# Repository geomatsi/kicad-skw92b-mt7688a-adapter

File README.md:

# Breadboard adapter for SKW92B WiFi module

Kicad project for [SKW92B](http://www.skylab.com.cn/uploadfile/Download/SkyLab_SKW92B_V1.06_datasheet.pdf) MT7688a WiFi module breadboard adapter.
SKW92B module integrates a 1x1 802.11n Wi-Fi radio, 580MHz MIPS CPU, 1-port Ethernet PHY, USB2.0 host, I2C/PCM and multiple slow GPIOs. 

Adapter schematics:

Adapter 3D view:

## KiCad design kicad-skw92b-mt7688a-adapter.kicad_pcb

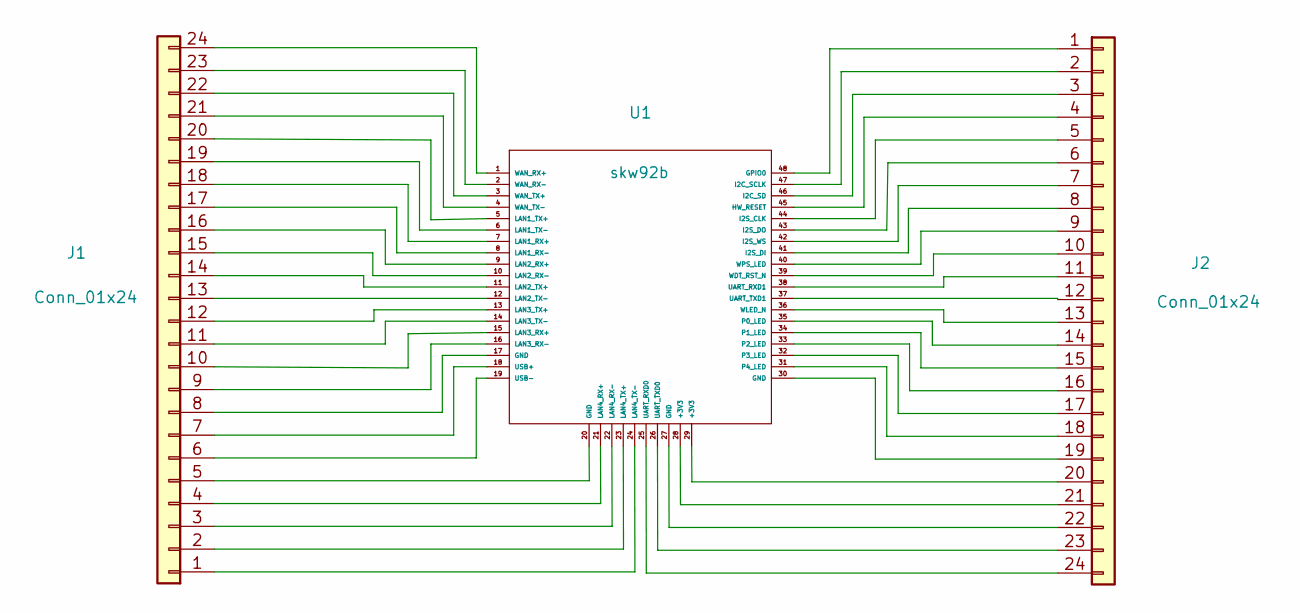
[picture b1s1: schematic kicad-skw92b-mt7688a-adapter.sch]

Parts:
J1, J2: Conn_01x24; PinHeader_1x24_P2.54mm_Vertical
U1: skw92b

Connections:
unnamed: J1.1, U1.24 (LAN4_TX-)
unnamed: J1.2, U1.23 (LAN4_TX+)
unnamed: J1.3, U1.22 (LAN4_RX-)
unnamed: J1.4, U1.21 (LAN4_RX+)
unnamed: J1.5, U1.20 (GND)
unnamed: J1.6, U1.19 (USB-)
unnamed: J1.7, U1.18 (USB+)
unnamed: J1.8, U1.17 (GND)
unnamed: J1.9, U1.16 (LAN3_RX-)
unnamed: J1.10, U1.15 (LAN3_RX+)
unnamed: J1.11, U1.14 (LAN3_TX-)
unnamed: J1.12, U1.13 (LAN3_TX+)
unnamed: J1.13, U1.12 (LAN2_TX-)
unnamed: J1.14, U1.11 (LAN2_TX+)
unnamed: J1.15, U1.10 (LAN2_RX-)
unnamed: J1.16, U1.9 (LAN2_RX+)
unnamed: J1.17, U1.8 (LAN1_RX-)
unnamed: J1.18, U1.7 (LAN1_RX+)
unnamed: J1.19, U1.6 (LAN1_TX-)
unnamed: J1.20, U1.5 (LAN1_TX+)
unnamed: J1.21, U1.4 (WAN_TX-)
unnamed: J1.22, U1.3 (WAN_TX+)
unnamed: J1.23, U1.2 (WAN_RX-)
unnamed: J1.24, U1.1 (WAN_RX+)
unnamed: J2.1, U1.48 (GPIO0)
unnamed: J2.2, U1.47 (I2C_SCLK)
unnamed: J2.3, U1.46 (I2C_SD)
unnamed: J2.4, U1.45 (HW_RESET)
unnamed: J2.5, U1.44 (I2S_CLK)
unnamed: J2.6, U1.43 (I2S_DO)
unnamed: J2.7, U1.42 (I2S_WS)
unnamed: J2.8, U1.41 (I2S_DI)
unnamed: J2.9, U1.40 (WPS_LED)
unnamed: J2.10, U1.39 (WDT_RST_N)
unnamed: J2.11, U1.38 (UART_RXD1)
unnamed: J2.12, U1.37 (UART_TXD1)
unnamed: J2.13, U1.36 (WLED_N)
unnamed: J2.14, U1.35 (P0_LED)
unnamed: J2.15, U1.34 (P1_LED)
unnamed: J2.16, U1.33 (P2_LED)
unnamed: J2.17, U1.32 (P3_LED)
unnamed: J2.18, U1.31 (P4_LED)
unnamed: J2.19, U1.30 (GND)
unnamed: J2.20, U1.29 (+3V3)
unnamed: J2.21, U1.28 (+3V3)
unnamed: J2.22, U1.27 (GND)
unnamed: J2.23, U1.26 (UART_TXD0)
unnamed: J2.24, U1.25 (UART_RXD0)

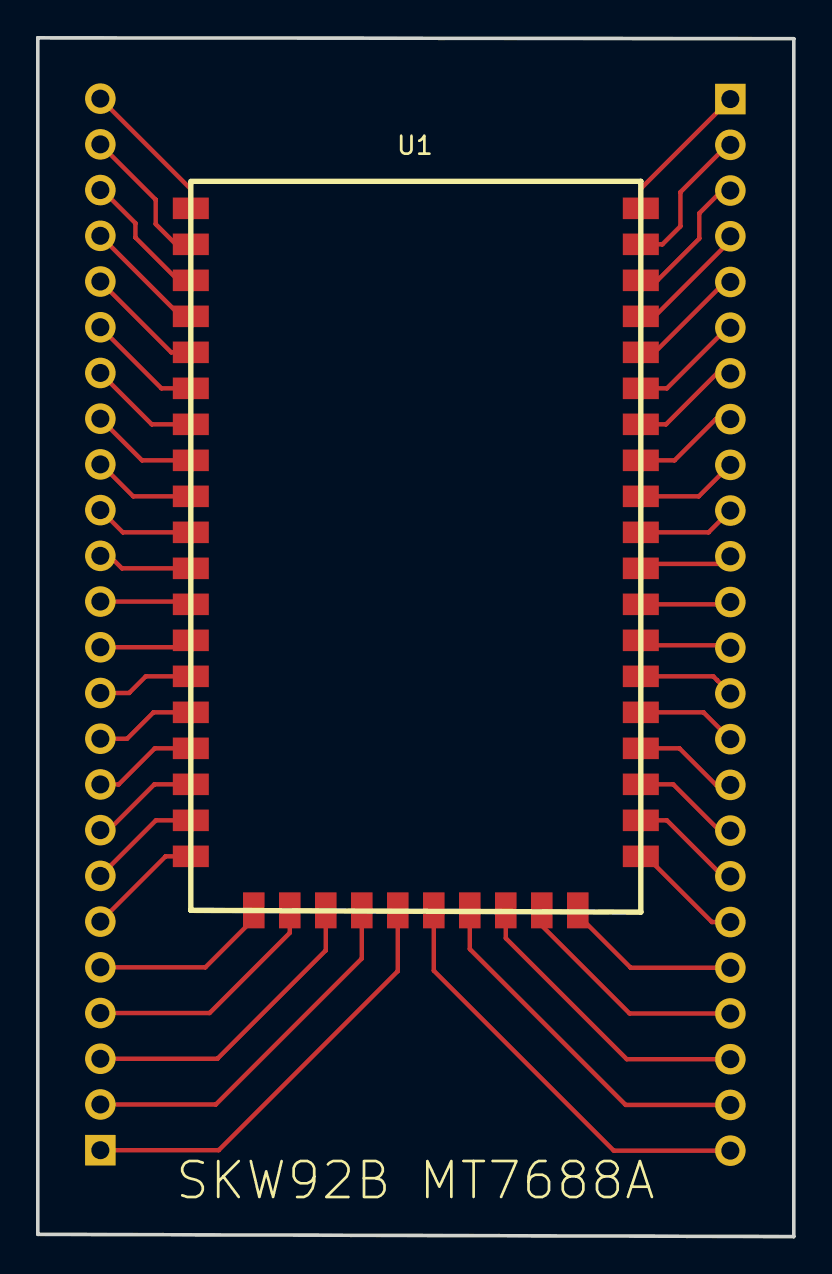
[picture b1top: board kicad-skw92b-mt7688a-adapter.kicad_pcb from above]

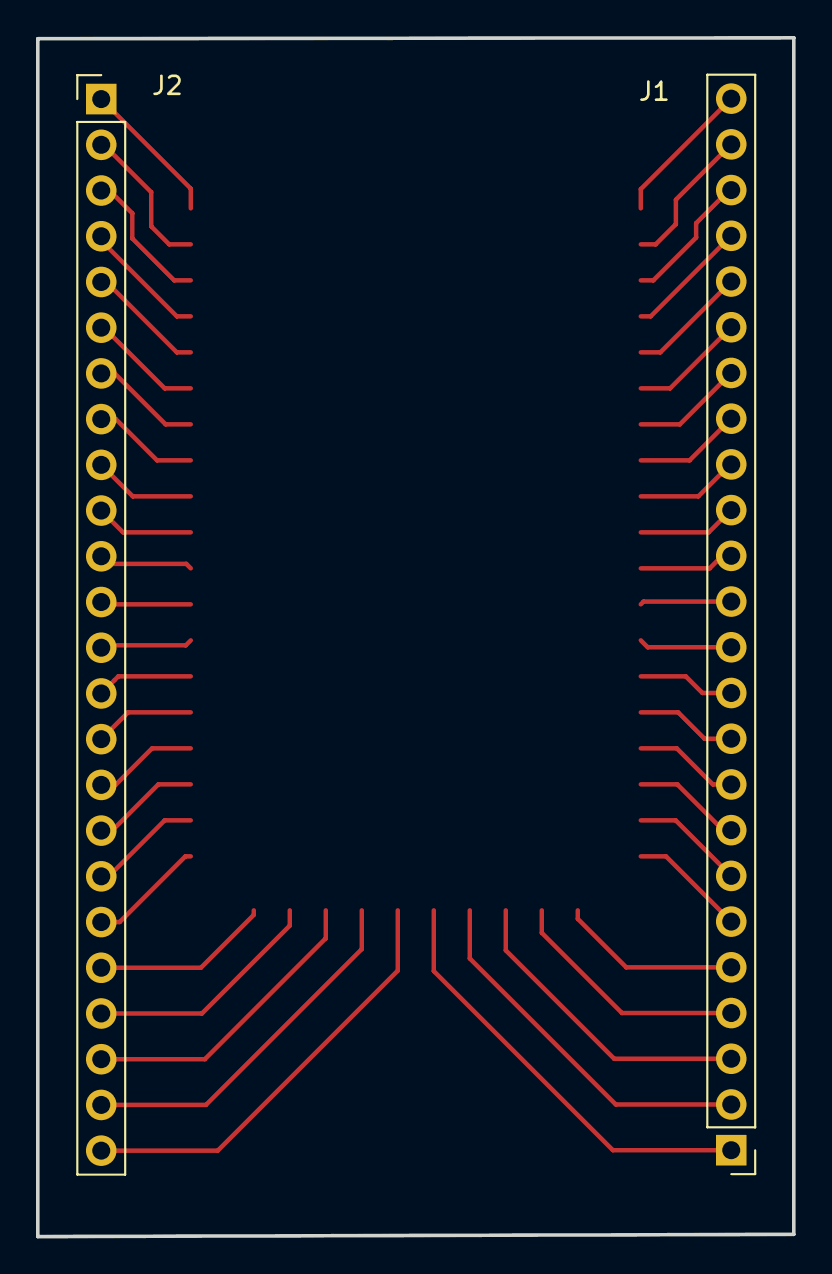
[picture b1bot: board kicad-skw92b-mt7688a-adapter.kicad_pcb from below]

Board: 2 copper layers, 42.0 x 66.6 mm, 3 parts (2 on the bottom side), 48 nets.

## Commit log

2020-07-23 skw92b: adapter for 2.54 breadboard
    Initial draft:
    - skw92b symbol (so far w/o footprint)
    - schematics
2020-07-24 skw92b: adapter for 2.54 breadboard
    - skw92b footprint created
    - pcb layout completed
2020-07-24 README: create brief overview
2020-07-26 generate gerber files
